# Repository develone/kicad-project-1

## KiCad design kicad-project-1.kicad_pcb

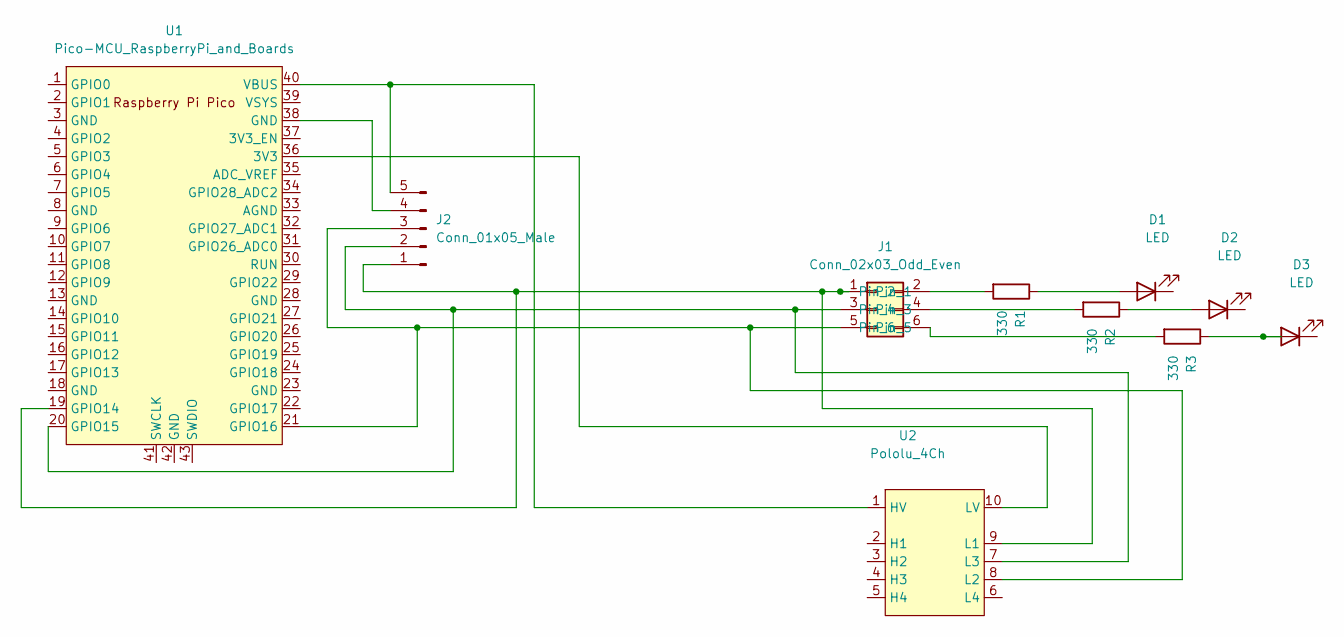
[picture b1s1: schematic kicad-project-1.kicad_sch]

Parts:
D1, D2, D3: LED; LED_D3.0mm
J1: Conn_02x03_Odd_Even; PinSocket_2x03_P2.00mm_Horizontal
J2: Conn_01x05_Male; PinSocket_1x05_P1.00mm_Vertical
R1, R2, R3: 330; R_0201_0603Metric
U1: Pico-MCU_RaspberryPi_and_Boards; DIP-40_W25.4mm_Socket_LongPads
U2: Pololu_4Ch; DIP-10_W7.62mm

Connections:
unnamed: D1.2 (A), R1.1
unnamed: D2.2 (A), R2.1
unnamed: D3.2 (A), R3.1
unnamed: J1.1, J2.1, U1.19 (GPIO14), U2.9 (L1)
unnamed: J1.2, R1.2
unnamed: J1.3, J2.2, U1.20 (GPIO15), U2.7 (L3)
unnamed: J1.4, R2.2
unnamed: J1.5, J2.3, U1.21 (GPIO16), U2.8 (L2)
unnamed: J1.6, R3.2
unnamed: J2.4, U1.38 (GND)
unnamed: J2.5, U1.40 (VBUS), U2.1 (HV)
unnamed: U1.36 (3V3), U2.10 (LV)

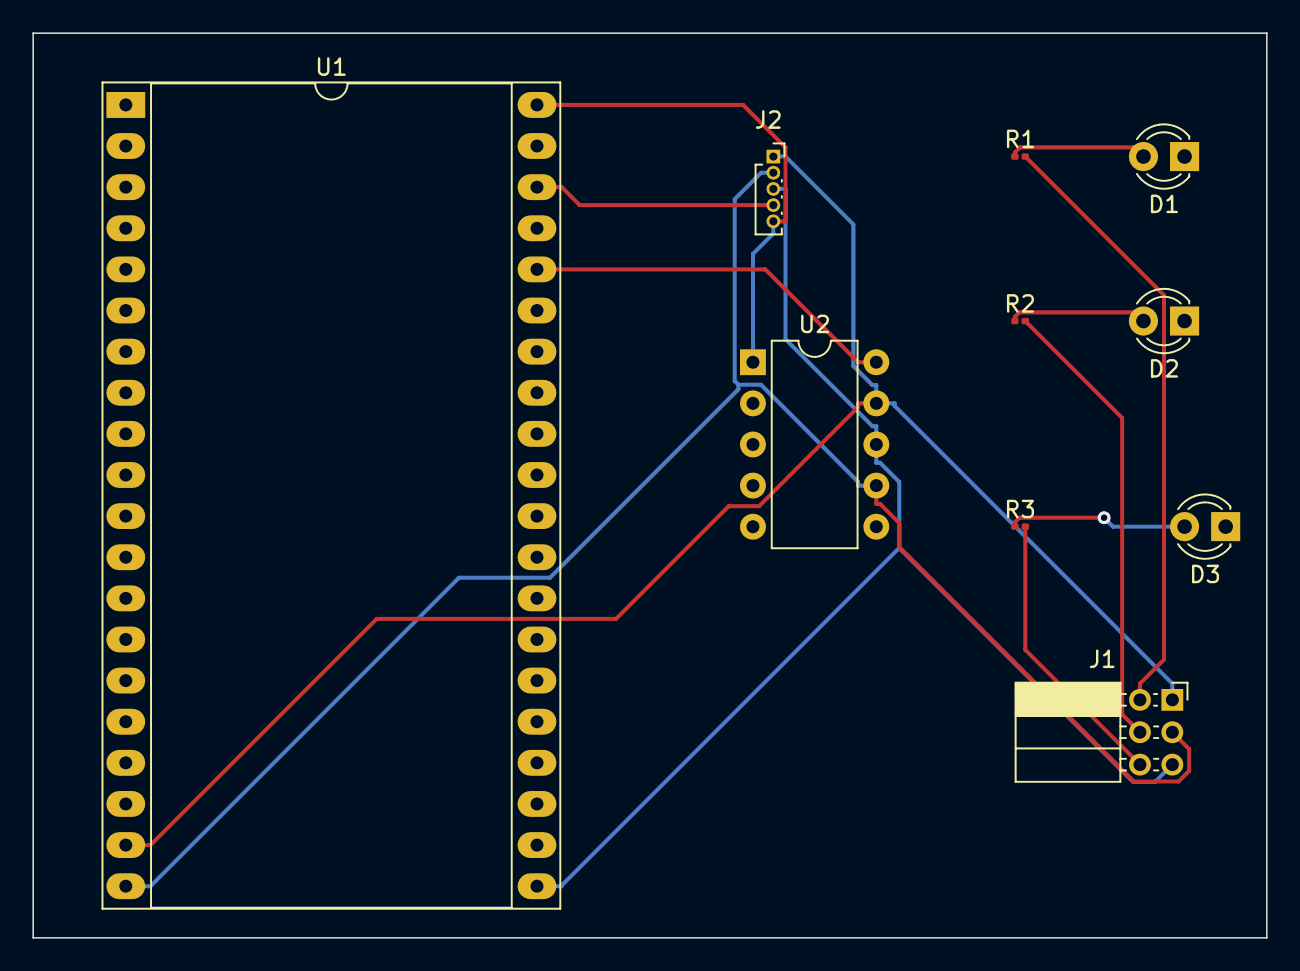
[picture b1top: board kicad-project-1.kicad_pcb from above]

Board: 2 copper layers, 76.2 x 55.9 mm, 10 parts (0 on the bottom side), 12 nets.

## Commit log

2023-08-10 Testing adding a new library for the symbol (kicad_symbol_lib (version 20211014) (generator kicad_symbol_editor) (symbol "Pololu_4Ch" (in_bom yes) (on_board yes) (property "Reference" "U" (id 0) (at 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
2023-08-10 adding needed files
2023-08-10 chg'ed missing_files/ missing_global_files
2023-08-10 testing making chgs on pi4-30 and transferring to pi4-60 for commit.
2023-08-10 diff --git a/missing_global_files/symbols/Polulu_Library.kicad_sym b/missing_global_files/symbols/Polulu_Library.kicad_sym index 341f4b9..c14d119 100644 --- a/missing_global_files/symbols/Polulu_Libr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
2023-08-11 update from pi4-50
2023-08-11 images as 08/11/2x
2023-08-11 testing
2024-04-18 from the pcb exported kicad-project-1.dsn and used java -jar freerouting-1.9.0.jar used kicad-project-1.dsn and did the routing. Then export Spectra Session file. kicad-project-1.ses This file was im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
2024-04-18 files created java -jar freerouting-1.9.0.jar
2024-04-18 update required
